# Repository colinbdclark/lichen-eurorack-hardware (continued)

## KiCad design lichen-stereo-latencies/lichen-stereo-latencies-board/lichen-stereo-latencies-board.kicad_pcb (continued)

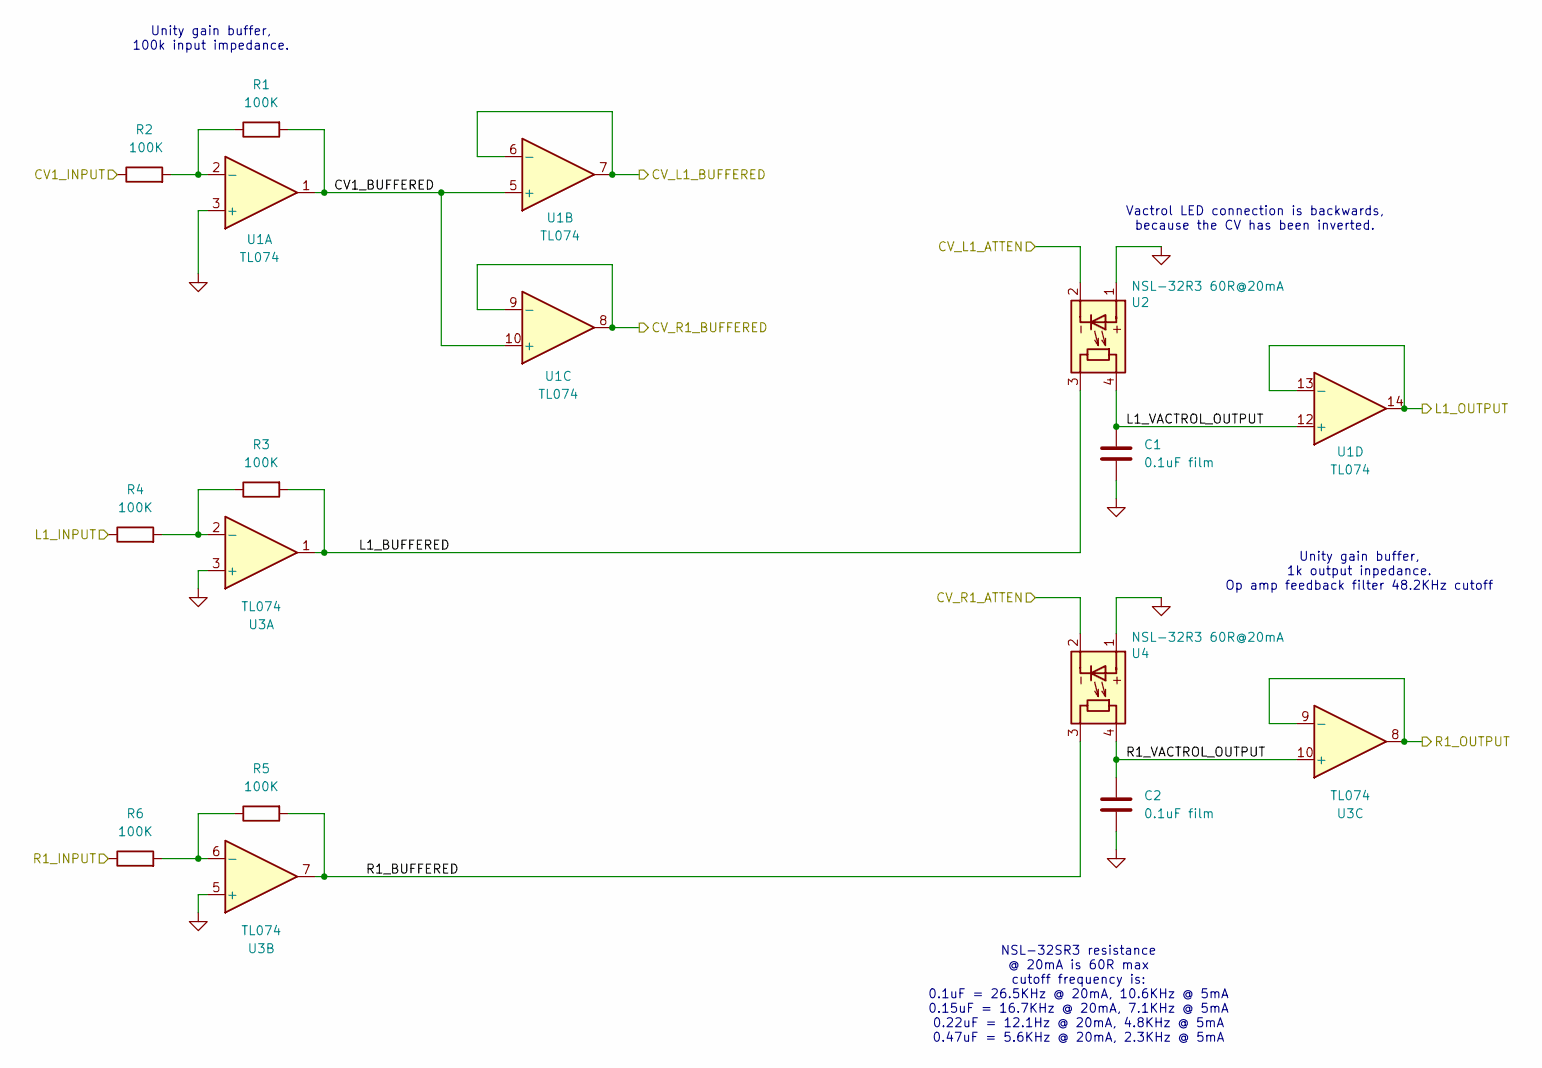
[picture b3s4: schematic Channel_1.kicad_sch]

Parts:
C1, C2: 0.1uF film; C_Rect_L7.2mm_W2.5mm_P5.00mm_FKS2_FKP2_MKS2_MKP2
R1, R2, R3, R4, R5, R6: 100K; R_0402_1005Metric; Part Number 0402WGF1003TCE; LCSC C25741
U1, U3: TL074; SOIC-14_3.9x8.7mm_P1.27mm; Part Number TL074IDR; LCSC C6964
U2, U4: NSL-32R3 60R@20mA; NSL-32; Part Number NSL-32SR3

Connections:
/Channel 1/CV1_BUFFERED: R1.2, U1.1, U1.5 (+), U1.10 (+)
/Channel 1/L1_BUFFERED: R3.2, U2.3 (R), U3.1
/Channel 1/L1_OUTPUT: U1.13 (-), U1.14; also elsewhere on the board
/Channel 1/L1_VACTROL_OUTPUT: C1.1, U1.12 (+), U2.4 (R)
/Channel 1/R1_BUFFERED: R5.2, U3.7, U4.3 (R)
/Channel 1/R1_VACTROL_OUTPUT: C2.1, U3.10 (+), U4.4 (R)
CV1_INPUT: R2.1; also elsewhere on the board
CV_L1_ATTEN: U2.2 (K); also elsewhere on the board
CV_L1_BUFFERED: U1.6 (-), U1.7; also elsewhere on the board
CV_R1_ATTEN: U4.2 (K); also elsewhere on the board
CV_R1_BUFFERED: U1.8, U1.9 (-); also elsewhere on the board
GND: C1.2, C2.2, U1.3 (+), U2.1 (A), U3.3 (+), U3.5 (+), U4.1 (A); also elsewhere on the board
L1_INPUT: R4.1; also elsewhere on the board
unnamed: R1.1, R2.2, U1.2 (-)
unnamed: R3.1, R4.2, U3.2 (-)
unnamed: R5.1, R6.2, U3.6 (-)
R1_INPUT: R6.1; also elsewhere on the board
R1_OUTPUT: U3.8, U3.9 (-); also elsewhere on the board

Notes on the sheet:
Unity gain buffer, 100k input impedance.
Unity gain buffer, 1k output inpedance. Op amp feedback filter 48.2KHz cutoff
NSL-32SR3 resistance @ 20mA is 60R max cutoff frequency is: 0.1uF = 26.5KHz @ 20mA, 10.6KHz @ 5mA 0.15uF = 16.7KHz @ 20mA, 7.1KHz @ 5mA 0.22uF = 12.1Hz @ 20mA, 4.8KHz @ 5mA 0.47uF = 5.6KHz @ 20mA, 2.3KHz @ 5mA
Vactrol LED connection is backwards, because the CV has been inverted.

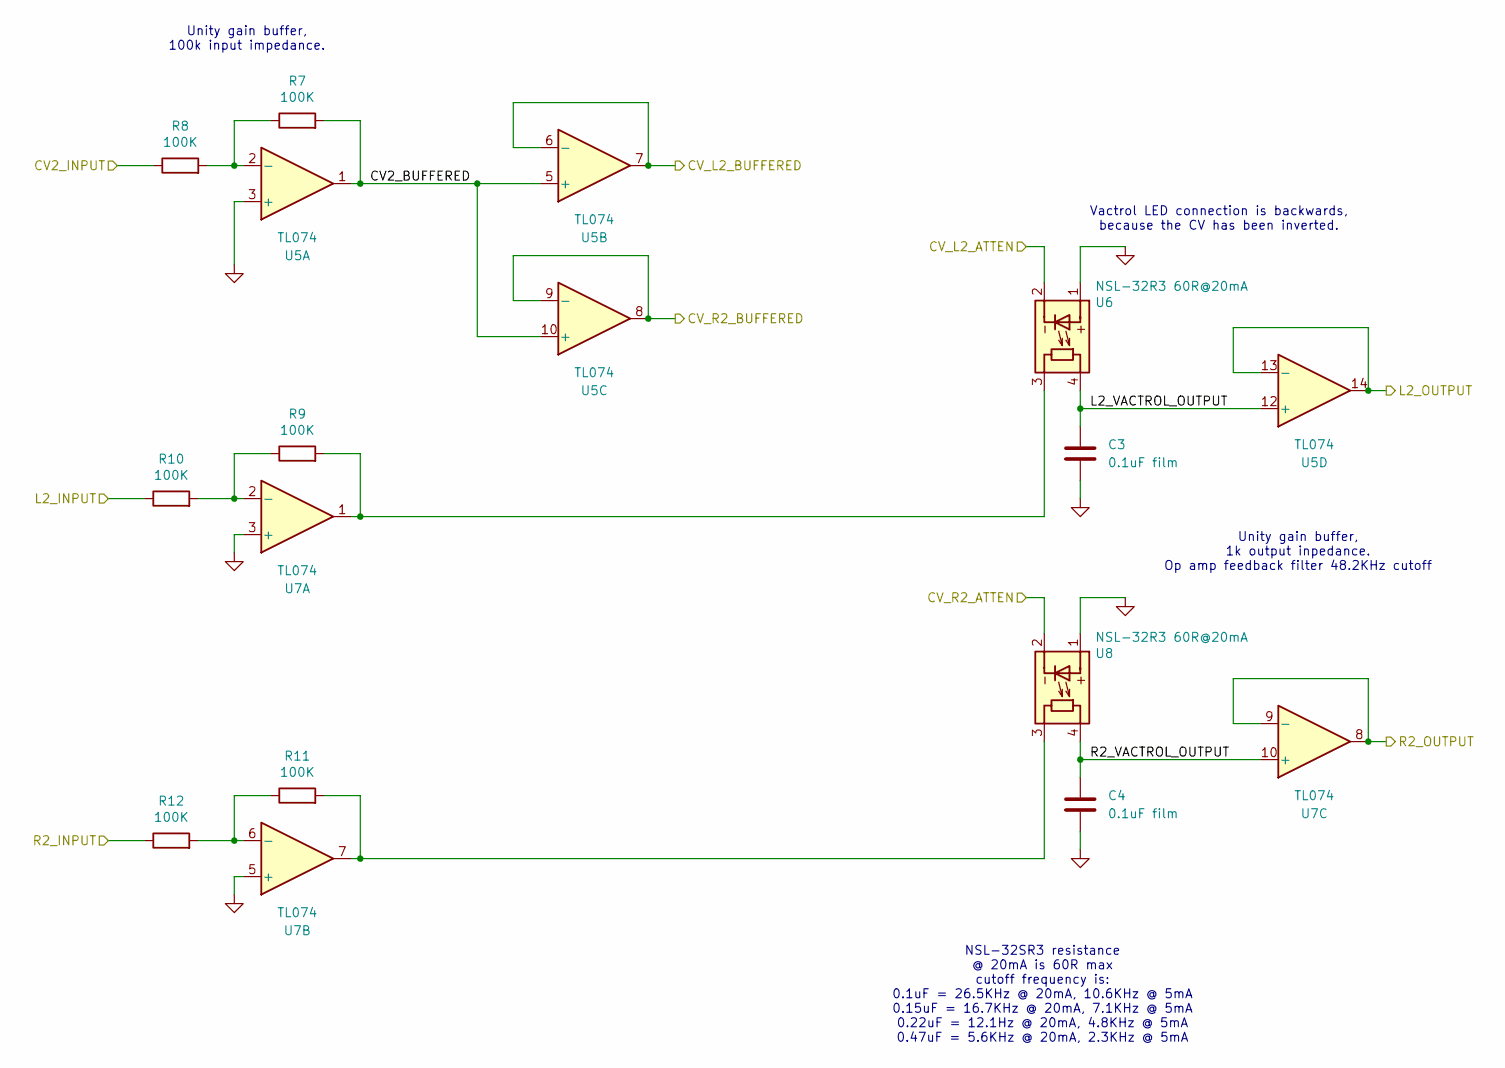
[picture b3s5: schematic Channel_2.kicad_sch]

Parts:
C3, C4: 0.1uF film; C_Rect_L7.2mm_W2.5mm_P5.00mm_FKS2_FKP2_MKS2_MKP2
R7, R8, R9, R10, R11, R12: 100K; R_0402_1005Metric; Part Number 0402WGF1003TCE; LCSC C25741
U5, U7: TL074; SOIC-14_3.9x8.7mm_P1.27mm; Part Number TL074IDR; LCSC C6964
U6, U8: NSL-32R3 60R@20mA; NSL-32; Part Number NSL-32SR3

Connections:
/Channel 2/CV2_BUFFERED: R7.2, U5.1, U5.5 (+), U5.10 (+)
/Channel 2/L2_OUTPUT: U5.13 (-), U5.14; also elsewhere on the board
/Channel 2/L2_VACTROL_OUTPUT: C3.1, U5.12 (+), U6.4 (R)
/Channel 2/R2_OUTPUT: U7.8, U7.9 (-); also elsewhere on the board
/Channel 2/R2_VACTROL_OUTPUT: C4.1, U7.10 (+), U8.4 (R)
CV2_INPUT: R8.1; also elsewhere on the board
CV_L2_ATTEN: U6.2 (K); also elsewhere on the board
CV_L2_BUFFERED: U5.6 (-), U5.7; also elsewhere on the board
CV_R2_ATTEN: U8.2 (K); also elsewhere on the board
CV_R2_BUFFERED: U5.8, U5.9 (-); also elsewhere on the board
GND: C3.2, C4.2, U5.3 (+), U6.1 (A), U7.3 (+), U7.5 (+), U8.1 (A); also elsewhere on the board
L2_INPUT: R10.1; also elsewhere on the board
unnamed: R9.2, U6.3 (R), U7.1
unnamed: R11.2, U7.7, U8.3 (R)
unnamed: R7.1, R8.2, U5.2 (-)
unnamed: R9.1, R10.2, U7.2 (-)
unnamed: R11.1, R12.2, U7.6 (-)
R2_INPUT: R12.1; also elsewhere on the board

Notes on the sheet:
NSL-32SR3 resistance @ 20mA is 60R max cutoff frequency is: 0.1uF = 26.5KHz @ 20mA, 10.6KHz @ 5mA 0.15uF = 16.7KHz @ 20mA, 7.1KHz @ 5mA 0.22uF = 12.1Hz @ 20mA, 4.8KHz @ 5mA 0.47uF = 5.6KHz @ 20mA, 2.3KHz @ 5mA
Unity gain buffer, 1k output inpedance. Op amp feedback filter 48.2KHz cutoff
Unity gain buffer, 100k input impedance.
Vactrol LED connection is backwards, because the CV has been inverted.

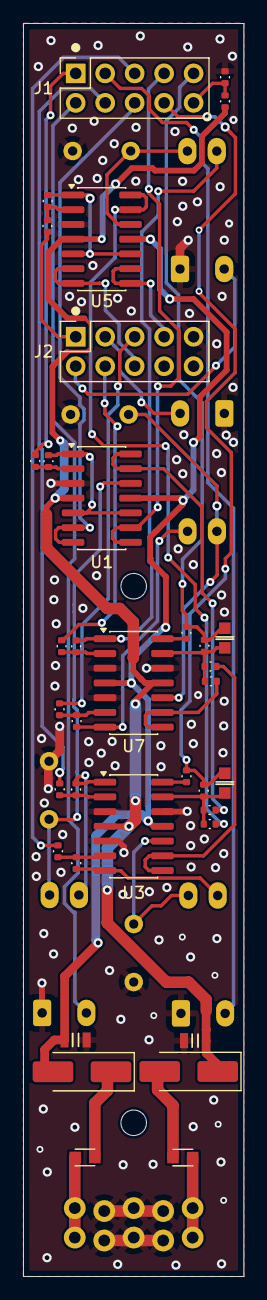
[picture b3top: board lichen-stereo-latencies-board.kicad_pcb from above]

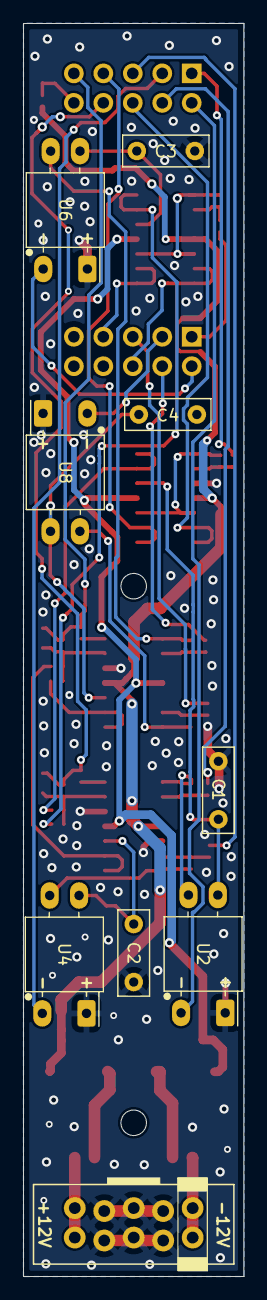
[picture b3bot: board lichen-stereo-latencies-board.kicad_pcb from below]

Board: 2 copper layers, 19.0 x 108.0 mm, 47 parts (9 on the bottom side), 48 nets.

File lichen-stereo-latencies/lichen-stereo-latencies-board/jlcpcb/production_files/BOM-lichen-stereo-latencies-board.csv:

Comment,Designator,Footprint,LCSC,Quantity
1K,"R15,R19",R_0402_1005Metric,C11702,2
FerriteBead_0603_2A,"L1,L2",R_0603,C14709,2
33pF C0G,"C5,C6",C_0603,C1663,2
100K,"R1,R10,R11,R12,R13,R14,R16,R17,R18,R2,R20,R3,R4,R5,R6,R7,R8,R9",R_0402_1005Metric,C25741,18
10K,R21,R_0402_1005Metric,C25744,1
12K,R22,R_0402_1005Metric,C25752,1
10uF,"C7,C8",C_0805,C440198,2
TL074,"U1,U3,U5,U7",SOIC-14_3.9x8.7mm_P1.27mm,C6964,4
Schottky,"D1,D2",D_SMA_Handsoldering,C8678,2

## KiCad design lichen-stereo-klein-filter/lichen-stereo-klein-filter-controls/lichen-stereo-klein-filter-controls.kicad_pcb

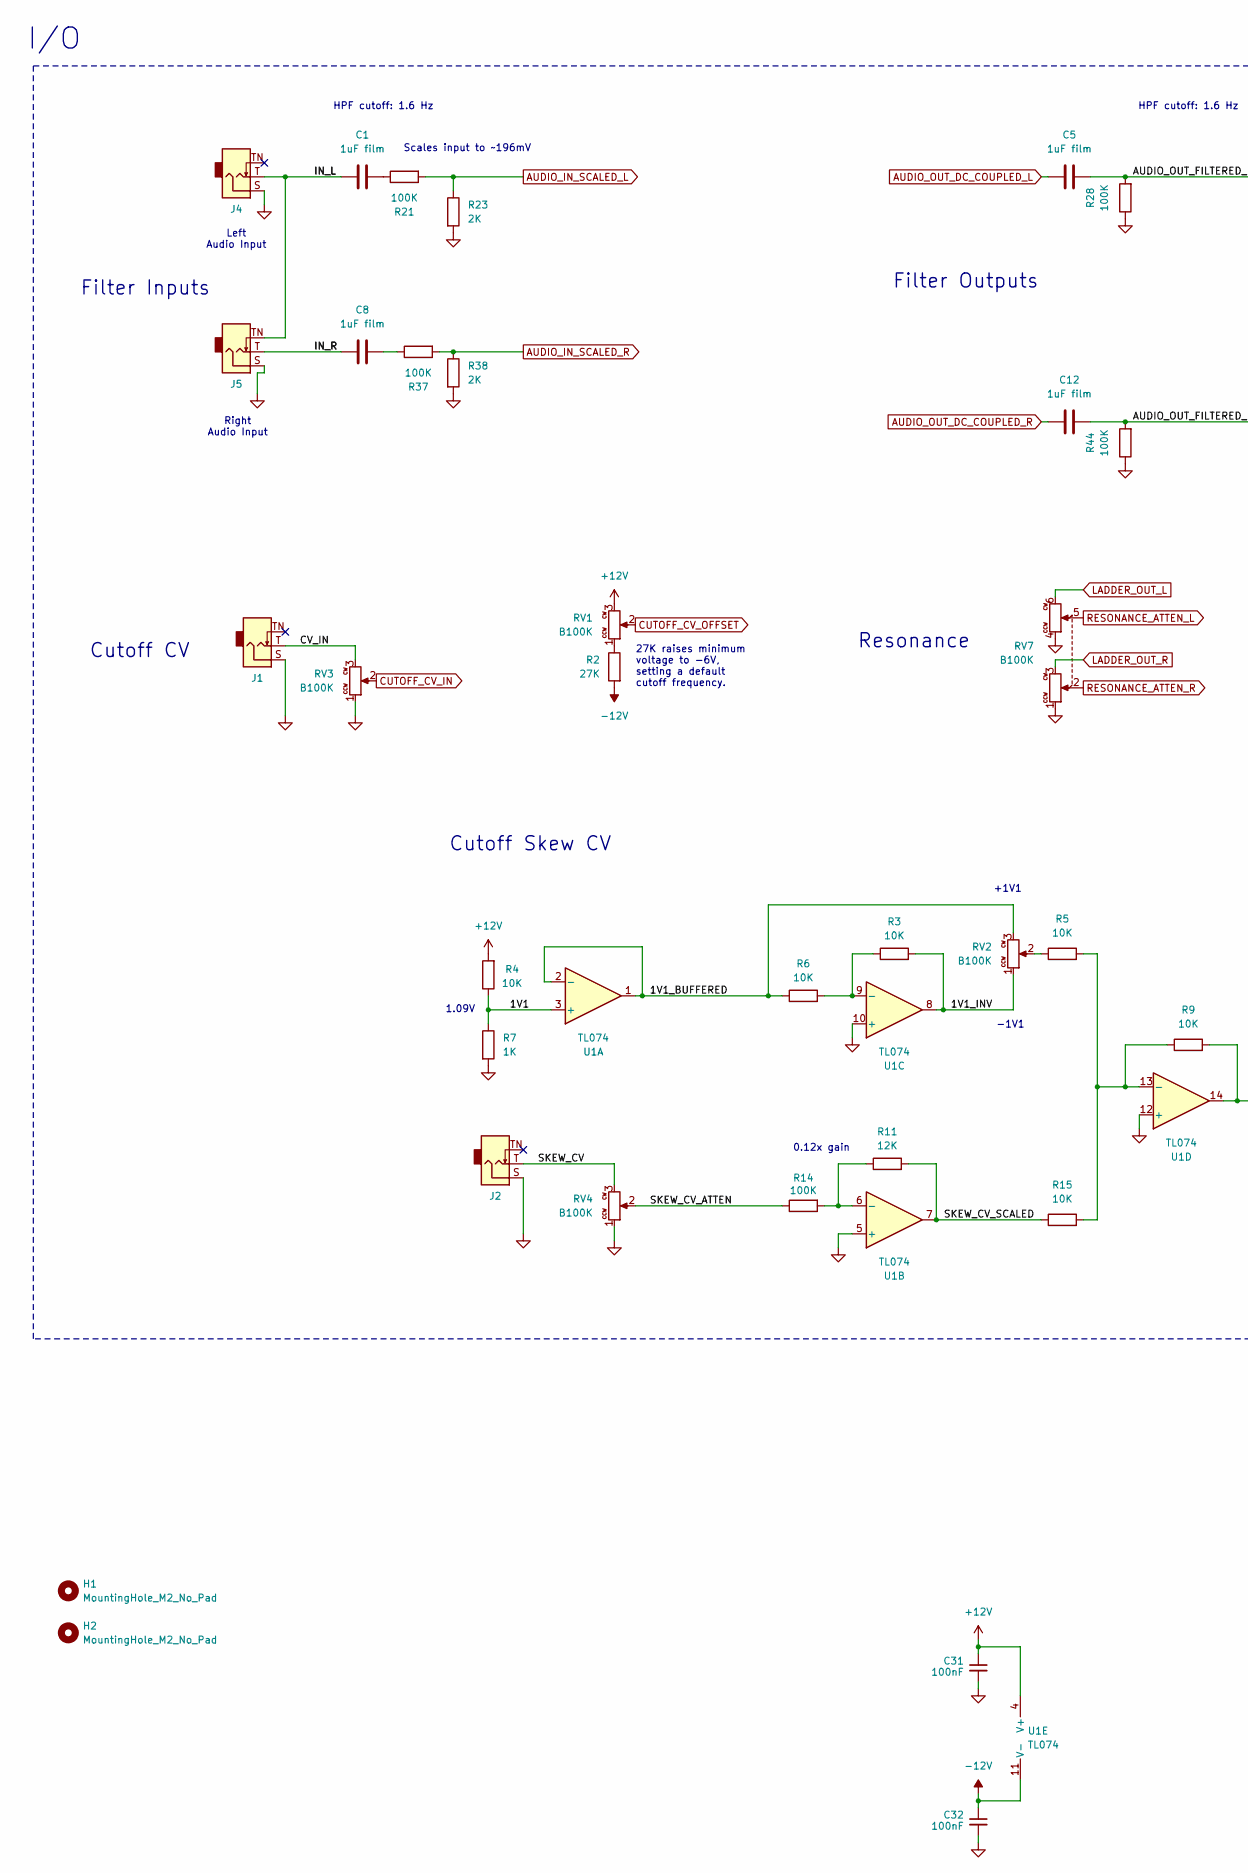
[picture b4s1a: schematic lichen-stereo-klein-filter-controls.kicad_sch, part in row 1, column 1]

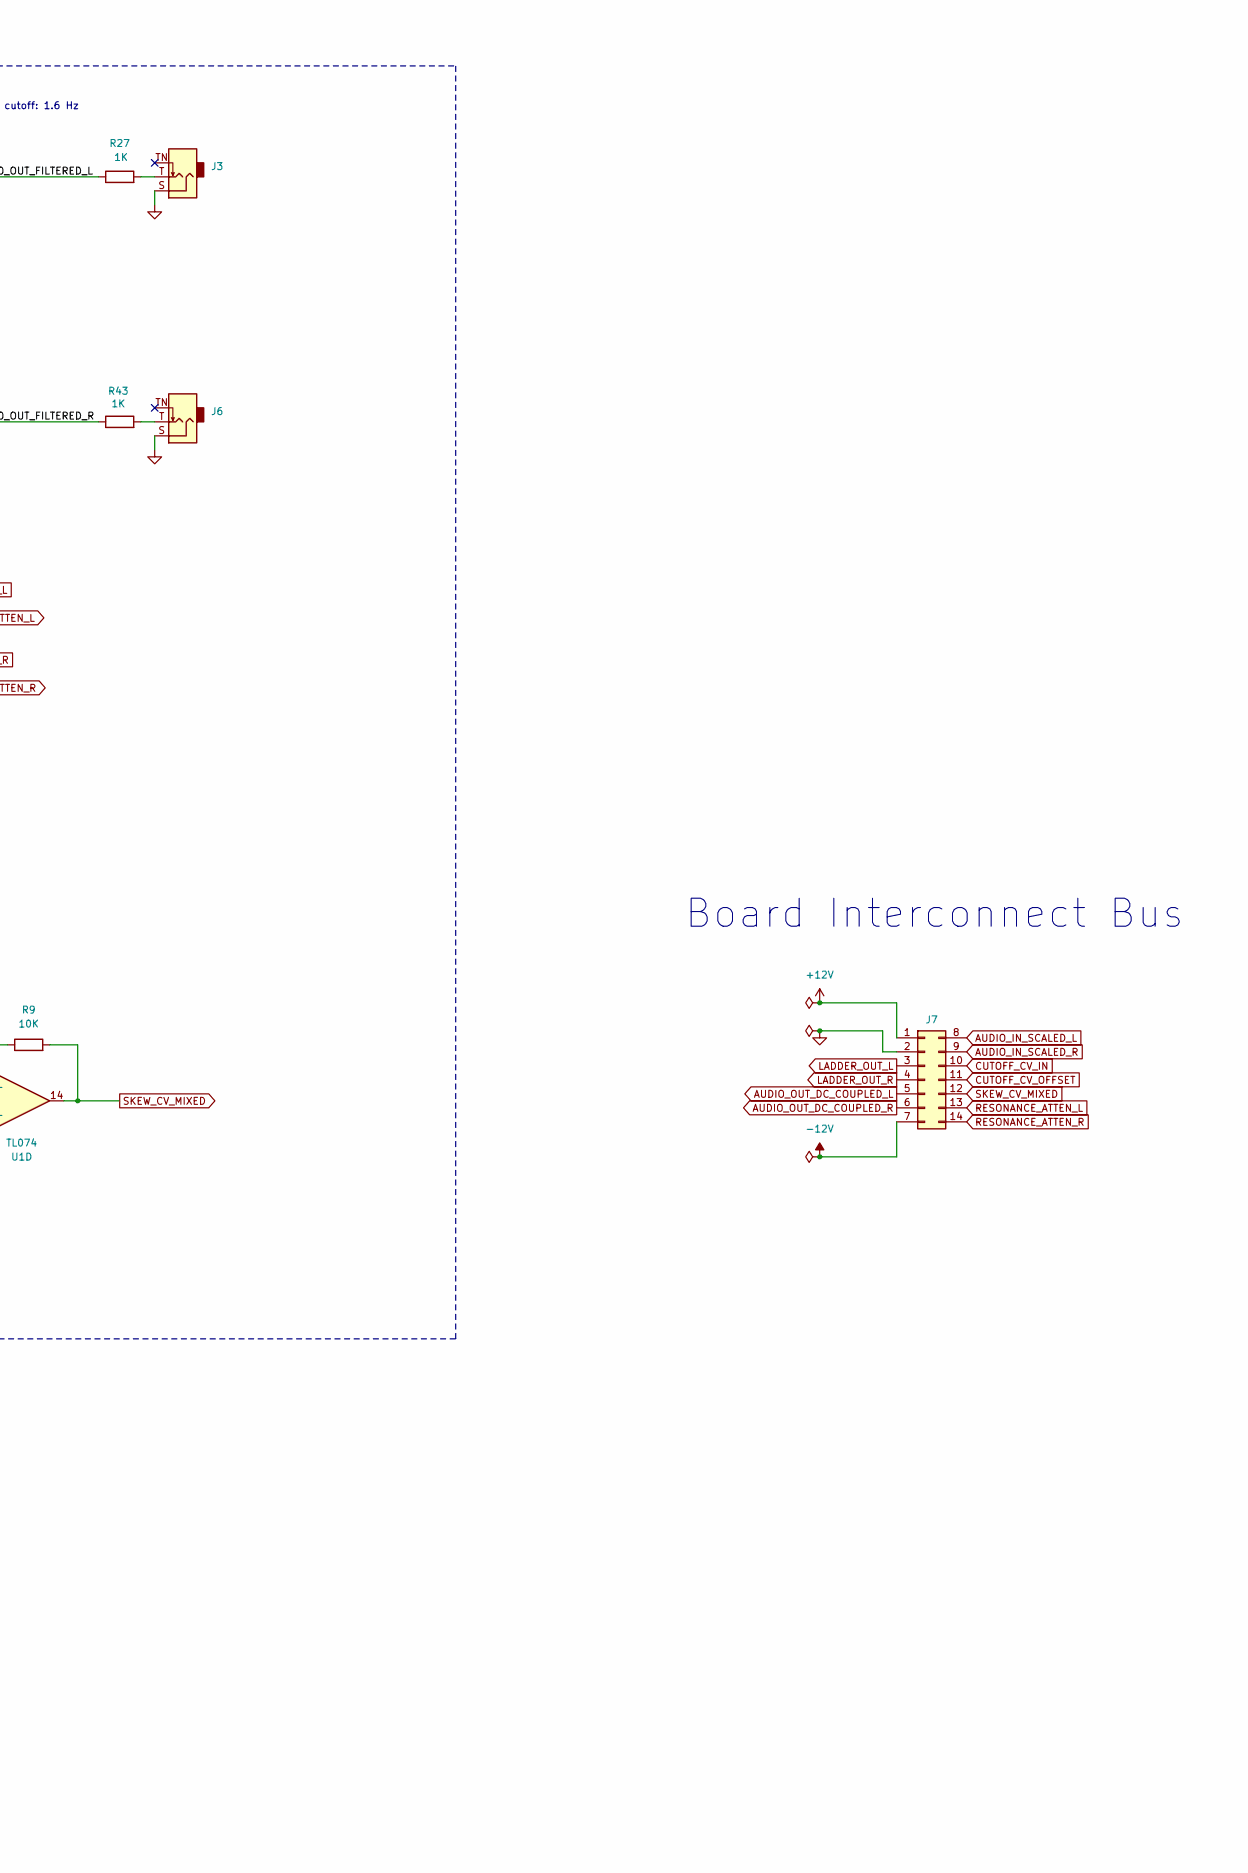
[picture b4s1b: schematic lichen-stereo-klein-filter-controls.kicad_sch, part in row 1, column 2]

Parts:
C1, C5, C8, C12: 1uF film; C_Rect_L7.2mm_W2.5mm_P5.00mm_FKS2_FKP2_MKS2_MKP2
C31, C32: 100nF; C_0402_1005Metric_small_pads; Part Number CL05B104KB54PNC; LCSC C307331
H1, H2: MountingHole_M2_No_Pad; MountingHole_2.2mm_M2
J1, J2: Thonkiconn_Mono_Audio_Jack; Audio_Jack_Thonkiconn_Mono; Part Number WQP518MA/PJ398SM
J3, J6: Thonkiconn_Mono_Audio_Jack; Audio_Jack_Thonkiconn_Mono_Right_Overhang; Part Number WQP518MA/PJ398SM
J4, J5: Thonkiconn_Mono_Audio_Jack; Audio_Jack_Thonkiconn_Mono_Left_Overhang; Part Number WQP518MA/PJ398SM
J7: 02x07 Socket; PinSocket_2x07_P2.54mm_Vertical_SMD; Part Number 2.54-2*7PFemale Headers; LCSC C84005
R2: 27K; R_0603; Part Number 0603WAF2702T5E; LCSC C22967
R3, R6, R9, R15: 10K; R_0603; Part Number 0603WAF1002T5E; LCSC C25804
R4, R5: 10K; R_0603; Part Number 0603WAF1002T5E; JLCPCB ID C25804
R7, R27, R43: 1K; R_0603; Part Number 0603WAF1001T5E; LCSC C21190
R11: 12K; R_0603; Part Number 0603WAF1202T5E; LCSC C22790
R14, R21, R28, R37, R44: 100K; R_0603; Part Number 0603WAF1003T5E; LCSC C25803
R23, R38: 2K; R_0603; Part Number 0603WAF2001T5E; LCSC C22975
RV1, RV2, RV3, RV4: B100K; Potentiometer_Alpha_RD901_Eurorack; Part Number RD901F-40
RV7: B100K; Potentiometer_Alpha_RD902F-40-00D_Dual_Vertical; Part Number RD90F-40
U1: TL074; SOIC-14_3.9x8.7mm_P1.27mm; Part Number TL074IDR; LCSC C6964

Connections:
+12V: C31.1, J7.1, R4.2, RV1.3, U1.4 (V+)
-12V: C32.1, J7.7, R2.2, U1.11 (V-)
/1V1: R4.1, R7.1, U1.3 (+)
/1V1_BUFFERED: R6.1, RV2.3, U1.1, U1.2 (-)
/1V1_INV: R3.2, RV2.1, U1.8
/AUDIO_OUT_FILTERED_L: C5.2, R27.1, R28.2
/AUDIO_OUT_FILTERED_R: C12.2, R43.1, R44.2
/CV_IN: J1.T, RV3.3
/IN_L: C1.1, J4.T, J5.TN
/IN_R: C8.1, J5.T
/SKEW_CV: J2.T, RV4.3
/SKEW_CV_ATTEN: R14.1, RV4.2
/SKEW_CV_SCALED: R11.2, R15.1, U1.7
AUDIO_IN_SCALED_L: J7.8, R21.2, R23.1
AUDIO_IN_SCALED_R: J7.9, R37.2, R38.1
AUDIO_OUT_DC_COUPLED_L: C5.1, J7.5
AUDIO_OUT_DC_COUPLED_R: C12.1, J7.6
CUTOFF_CV_IN: J7.10, RV3.2
CUTOFF_CV_OFFSET: J7.11, RV1.2
GND: C31.2, C32.2, J1.S, J2.S, J3.S, J4.S, J5.S, J6.S, J7.2, R7.2, R23.2, R28.1, R38.2, R44.1, RV3.1, RV4.1, RV7.1, RV7.4, U1.5 (+), U1.10 (+), U1.12 (+)
LADDER_OUT_L: J7.3, RV7.6
LADDER_OUT_R: J7.4, RV7.3
unnamed: C1.2, R21.1
unnamed: C8.2, R37.1
unnamed: J3.T, R27.2
unnamed: J6.T, R43.2
unnamed: R2.1, RV1.1
unnamed: R5.1, RV2.2
unnamed: R11.1, R14.2, U1.6 (-)
unnamed: R3.1, R6.2, U1.9 (-)
unnamed: R5.2, R9.1, R15.2, U1.13 (-)
RESONANCE_ATTEN_L: J7.13, RV7.5
RESONANCE_ATTEN_R: J7.14, RV7.2
SKEW_CV_MIXED: J7.12, R9.2, U1.14

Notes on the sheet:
Filter Outputs
HPF cutoff: 1.6 Hz
Resonance
Cutoff Skew CV
I/O
Scales input to ~196mV
Left Audio Input
Cutoff CV
-1V1
+1V1
Filter Inputs
0.12x gain
Right Audio Input
Board Interconnect Bus
1.09V
27K raises minimum voltage to -6V, setting a default cutoff frequency.

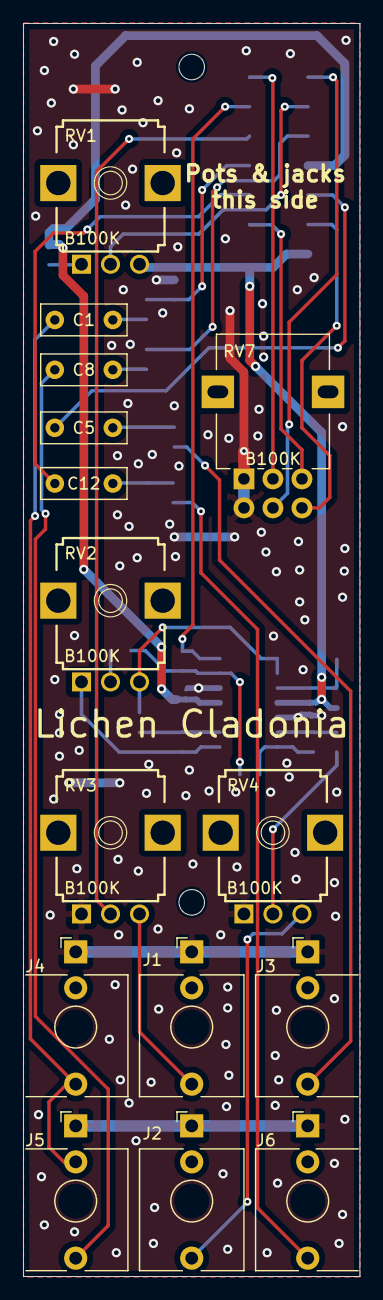
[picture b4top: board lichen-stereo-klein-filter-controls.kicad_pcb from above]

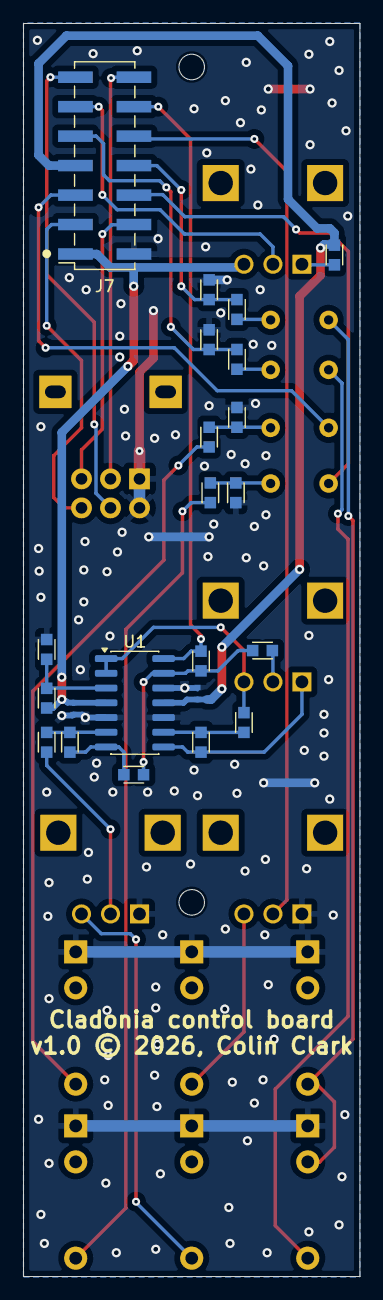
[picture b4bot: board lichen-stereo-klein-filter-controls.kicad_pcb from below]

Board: 2 copper layers, 29.0 x 108.0 mm, 39 parts (22 on the bottom side), 34 nets.

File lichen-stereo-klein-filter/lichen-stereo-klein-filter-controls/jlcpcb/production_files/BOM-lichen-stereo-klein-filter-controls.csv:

Comment,Designator,Footprint,LCSC,Quantity
1K,"R27,R43,R7",R_0603,C21190,3
12K,R11,R_0603,C22790,1
27K,R2,R_0603,C22967,1
2K,"R23,R38",R_0603,C22975,2
100K,"R14,R21,R28,R37,R44",R_0603,C25803,5
10K,"R15,R3,R4,R5,R6,R9",R_0603,C25804,6
100nF,"C31,C32",C_0402_1005Metric_small_pads,C307331,2
TL074,U1,SOIC-14_3.9x8.7mm_P1.27mm,C6964,1
02x07 Socket,J7,PinSocket_2x07_P2.54mm_Vertical_SMD,C84005,1

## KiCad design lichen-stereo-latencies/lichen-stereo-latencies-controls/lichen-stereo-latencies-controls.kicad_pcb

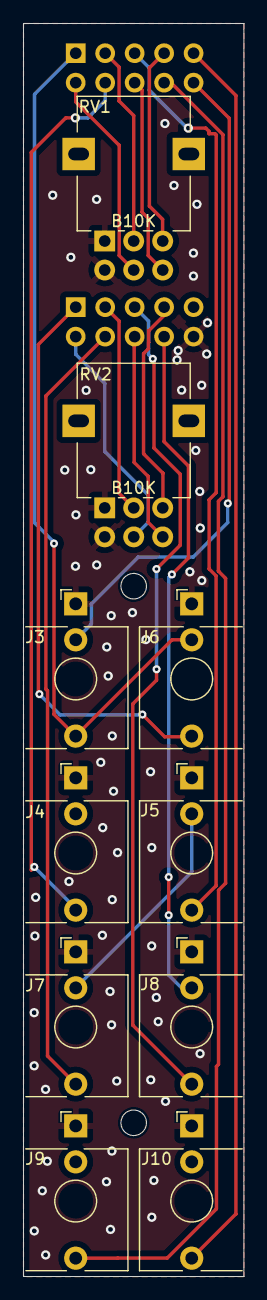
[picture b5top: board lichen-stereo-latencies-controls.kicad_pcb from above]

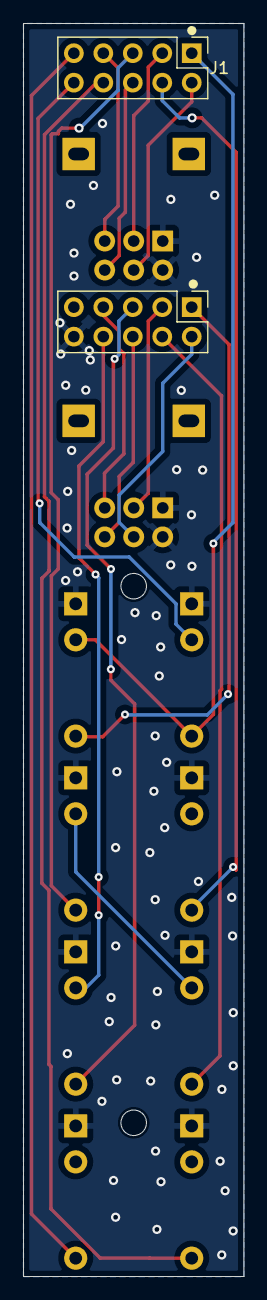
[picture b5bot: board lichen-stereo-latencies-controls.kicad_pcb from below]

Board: 2 copper layers, 19.0 x 108.0 mm, 14 parts (2 on the bottom side), 20 nets.

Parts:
H1, H2: MountingHole_M2_No_Pad; MountingHole_2.2mm_M2
J1: 02x05 Pins; PinHeader_2x05_P2.54mm_Vertical
J2: 2x5 Pins; PinHeader_2x05_P2.54mm_Vertical
J3, J4, J7, J9: Thonkiconn_Mono_Audio_Jack; Audio_Jack_Thonkiconn_Mono_Left_Overhang
J5, J6, J8, J10: Thonkiconn_Mono_Audio_Jack; Audio_Jack_Thonkiconn_Mono_Right_Overhang
RV1, RV2: B10K; Potentiometer_Alpha_RD902F-40-00D_Dual_Vertical

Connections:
CV1_INPUT: J1.1, J3.T, J6.TN
CV2_INPUT: J2.1, J6.T
CV_L1_ATTEN: J1.2, RV1.5
CV_L1_BUFFERED: J1.6, RV1.6
CV_L2_ATTEN: J2.2, RV2.5
CV_L2_BUFFERED: J2.6, RV2.6
CV_NORM_5V: J1.10, J3.TN
CV_R1_ATTEN: J1.3, RV1.2
CV_R1_BUFFERED: J1.7, RV1.3
CV_R2_ATTEN: J2.3, RV2.2
CV_R2_BUFFERED: J2.7, RV2.3
GND: J2.10, J3.S, J4.S, J5.S, J6.S, J7.S, J8.S, J9.S, J10.S, RV1.1, RV1.4, RV2.1, RV2.4
L1_INPUT: J1.4, J4.T
L1_OUTPUT: J5.TN, J7.TN
L2_INPUT: J2.4, J7.T
L_OUTPUT: J1.8, J9.T
R1_INPUT: J1.5, J5.T
R1_OUTPUT: J2.8, J8.TN
R2_INPUT: J2.5, J8.T
R_OUTPUT: J1.9, J10.T

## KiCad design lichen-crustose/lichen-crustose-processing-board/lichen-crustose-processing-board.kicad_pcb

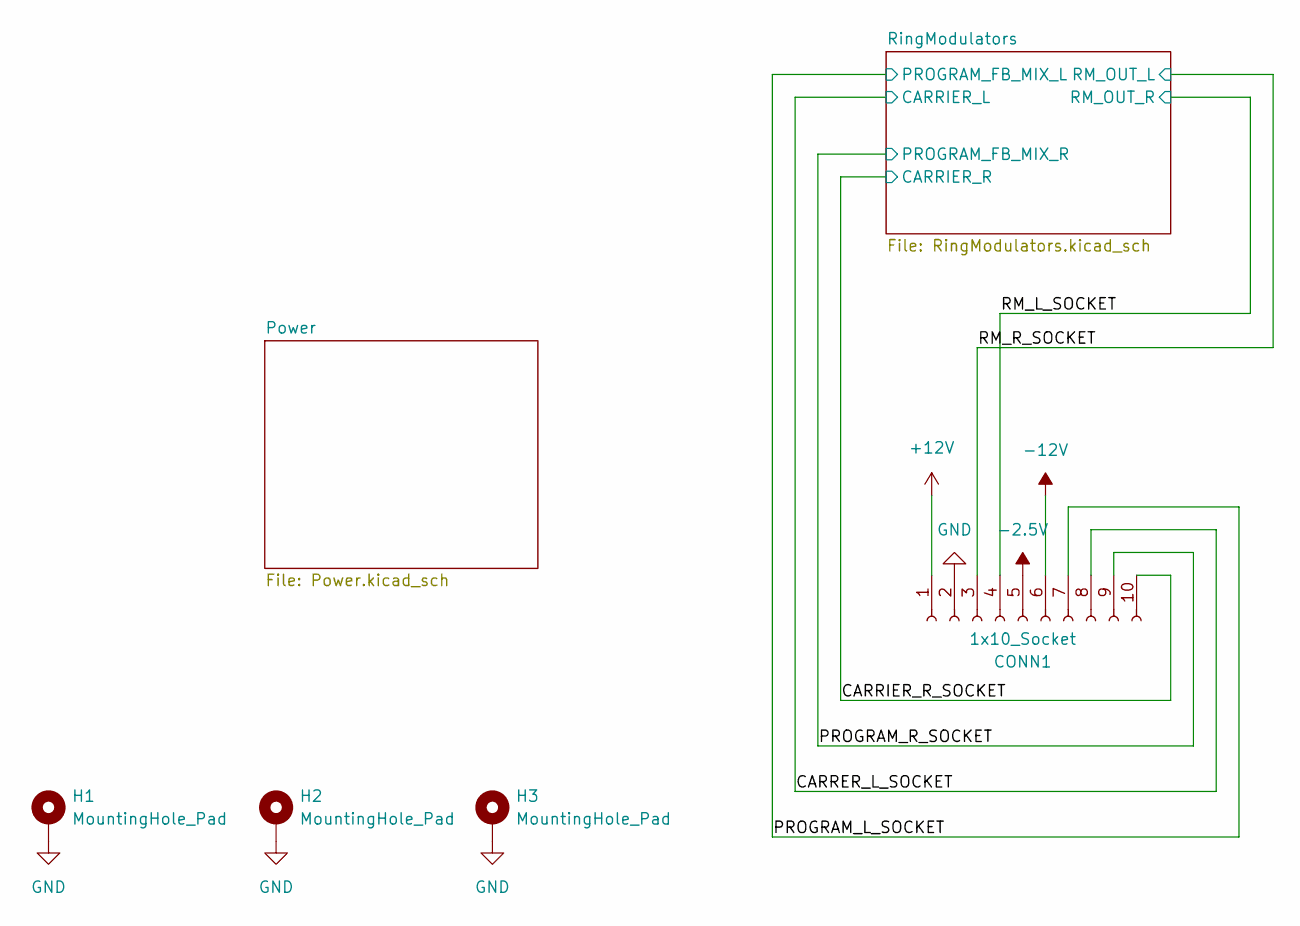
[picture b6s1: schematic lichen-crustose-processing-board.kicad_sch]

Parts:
CONN1: 1x10_Socket; PinSocket_1x10_P2.54mm_Vertical
H1, H2, H3: MountingHole_Pad; MountingHole_2.2mm_M2_Pad

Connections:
+12V: CONN1.1; also elsewhere on the board
-2.5V: CONN1.5; also elsewhere on the board
-12V: CONN1.6; also elsewhere on the board
/CARRER_L_SOCKET: CONN1.8; also elsewhere on the board
/CARRIER_R_SOCKET: CONN1.10; also elsewhere on the board
/PROGRAM_L_SOCKET: CONN1.7; also elsewhere on the board
/PROGRAM_R_SOCKET: CONN1.9; also elsewhere on the board
/RM_L_SOCKET: CONN1.4; also elsewhere on the board
/RM_R_SOCKET: CONN1.3; also elsewhere on the board
GND: CONN1.2, H1.1, H2.1, H3.1; also elsewhere on the board

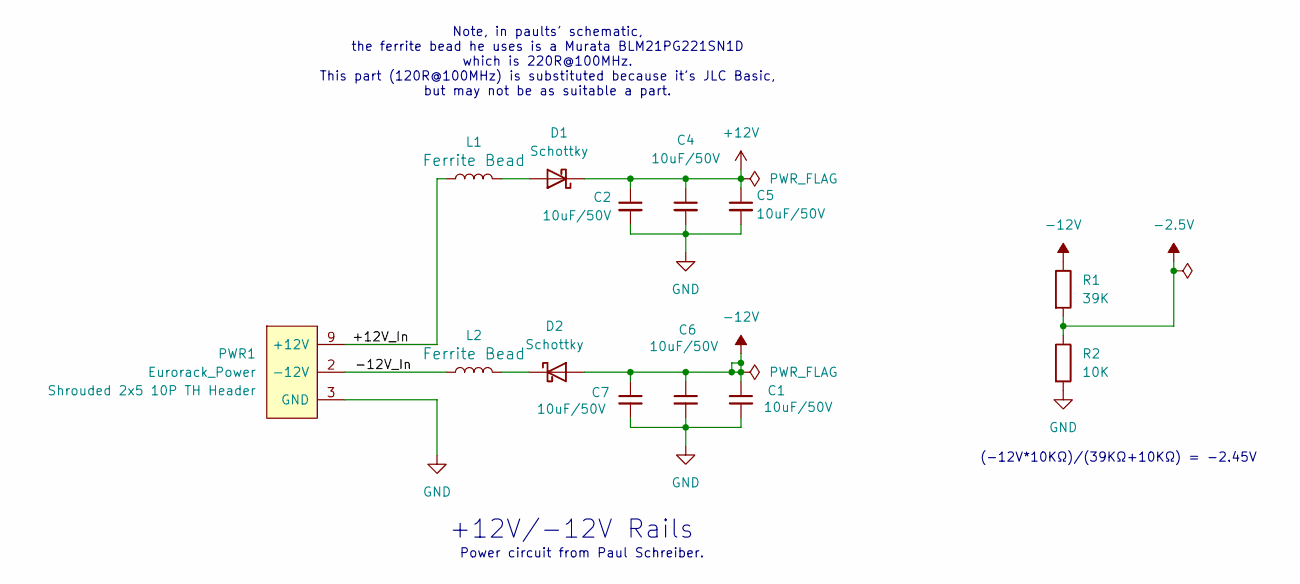
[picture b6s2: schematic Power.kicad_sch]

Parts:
C1, C2, C4, C5, C6, C7: 10uF; C_0805; Part Number GRM21BR61H106KE43L; LCSC C440198
D1, D2: Schottky; D_SMA_Handsoldering; Part Number SS34; LCSC C8678
L1, L2: FerriteBead_0603_2A; R_0603; Part Number BLM18PG121SN1D; LCSC C14709
PWR1: Eurorack_Power; Eurorack_Power_Shrouded_TH_Staggered
R1: 39K; R_0603; Part Number 0603WAF3902T5E; LCSC C23153
R2: 10K; R_0603; Part Number 0603WAF1002T5E; LCSC C25804

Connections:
+12V: C2.1, C4.1, C5.1, D1.1 (K); also elsewhere on the board
-2.5V: R1.2, R2.1; also elsewhere on the board
-12V: C1.1, C6.1, C7.1, D2.2 (A), R1.1; also elsewhere on the board
/Power/+12V_In: L1.1, PWR1.9 (+12V), PWR1.10 (+12V)
/Power/-12V_In: L2.1, PWR1.1 (-12V), PWR1.2 (-12V)
GND: C1.2, C2.2, C4.2, C5.2, C6.2, C7.2, PWR1.3 (GND), PWR1.4 (GND), PWR1.5 (GND), PWR1.6 (GND), PWR1.7 (GND), PWR1.8 (GND), R2.2; also elsewhere on the board
unnamed: D1.2 (A), L1.2
unnamed: D2.1 (K), L2.2

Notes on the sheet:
Note, in paults' schematic, the ferrite bead he uses is a Murata BLM21PG221SN1D which is 220R@100MHz. This part (120R@100MHz) is substituted because it's JLC Basic, but may not be as suitable a part.
(-12V*10KΩ)/(39KΩ+10KΩ) = -2.45V
Power circuit from Paul Schreiber.
+12V/-12V Rails

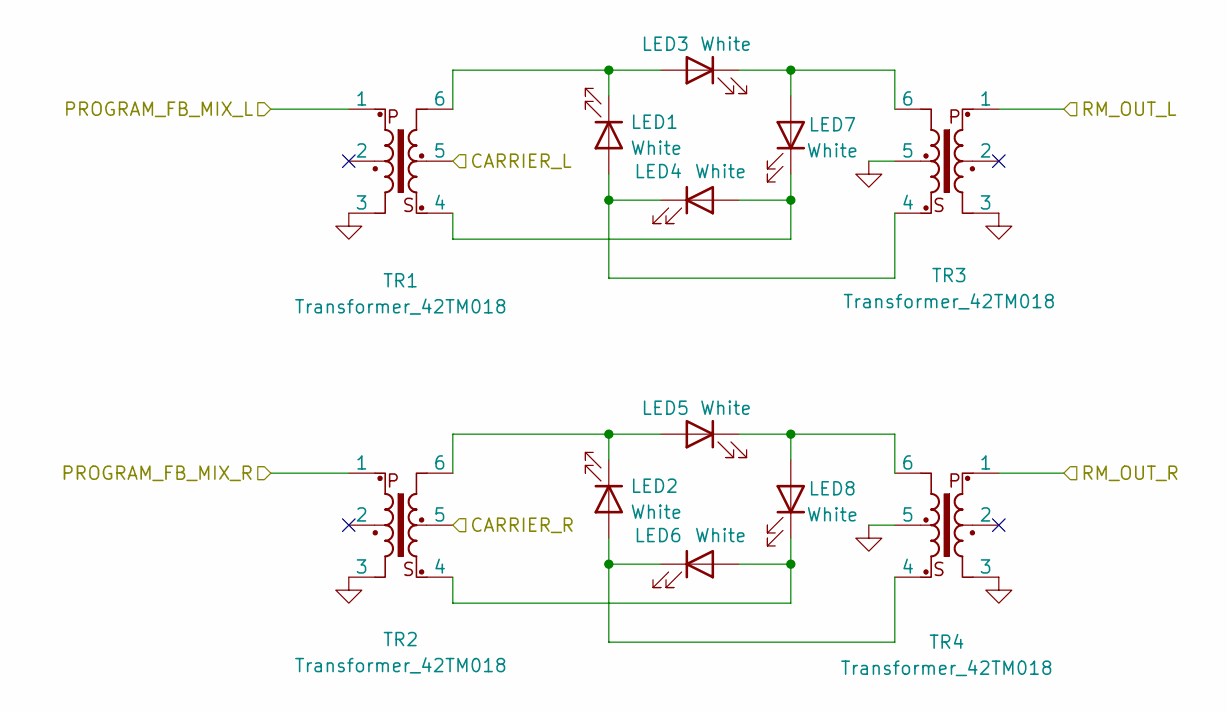
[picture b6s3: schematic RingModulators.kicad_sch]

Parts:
LED1, LED2, LED3, LED4, LED5, LED6, LED7, LED8: White; LED_D3.0mm_Polarity_Indicated
TR1, TR2, TR3, TR4: Transformer_42TM018; 42TM018

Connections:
/CARRER_L_SOCKET: TR1.5; also elsewhere on the board
/CARRIER_R_SOCKET: TR2.5; also elsewhere on the board
/PROGRAM_L_SOCKET: TR1.1; also elsewhere on the board
/PROGRAM_R_SOCKET: TR2.1; also elsewhere on the board
/RM_L_SOCKET: TR4.1; also elsewhere on the board
/RM_R_SOCKET: TR3.1; also elsewhere on the board
GND: TR1.3, TR2.3, TR3.3, TR3.5, TR4.3, TR4.5; also elsewhere on the board
unnamed: LED1.2 (A), LED4.1 (K), TR3.4
unnamed: LED1.1 (K), LED3.2 (A), TR1.6
unnamed: LED2.2 (A), LED6.1 (K), TR4.4
unnamed: LED2.1 (K), LED5.2 (A), TR2.6
unnamed: LED3.1 (K), LED7.2 (A), TR3.6
unnamed: LED4.2 (A), LED7.1 (K), TR1.4
unnamed: LED5.1 (K), LED8.2 (A), TR4.6
unnamed: LED6.2 (A), LED8.1 (K), TR2.4

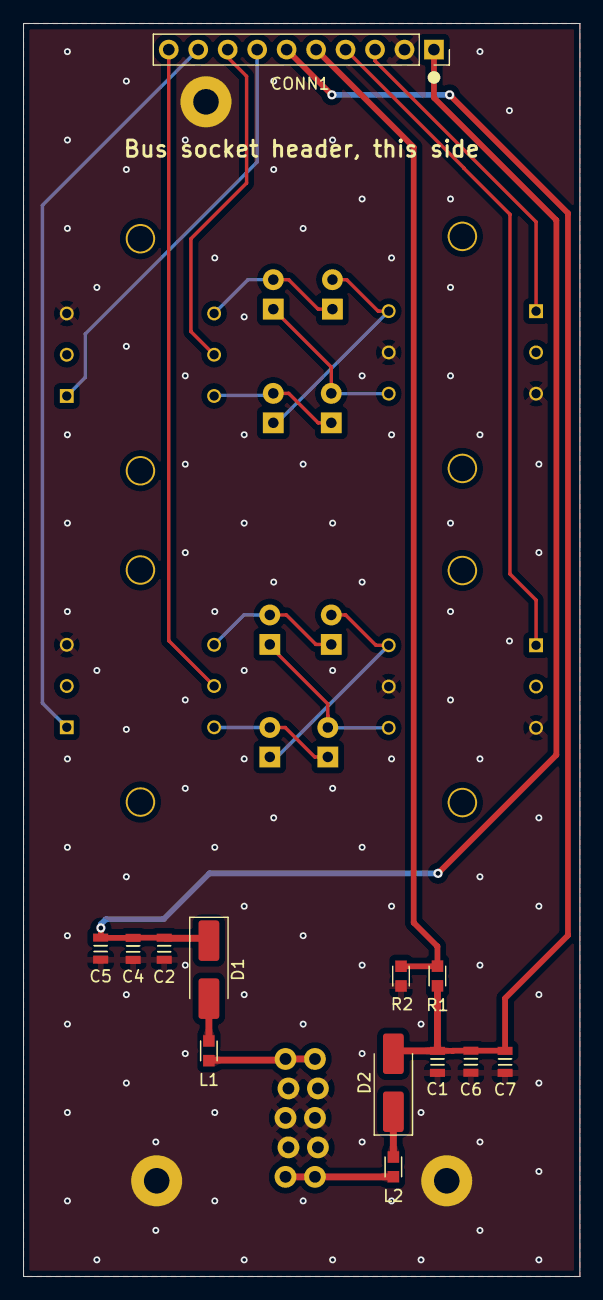
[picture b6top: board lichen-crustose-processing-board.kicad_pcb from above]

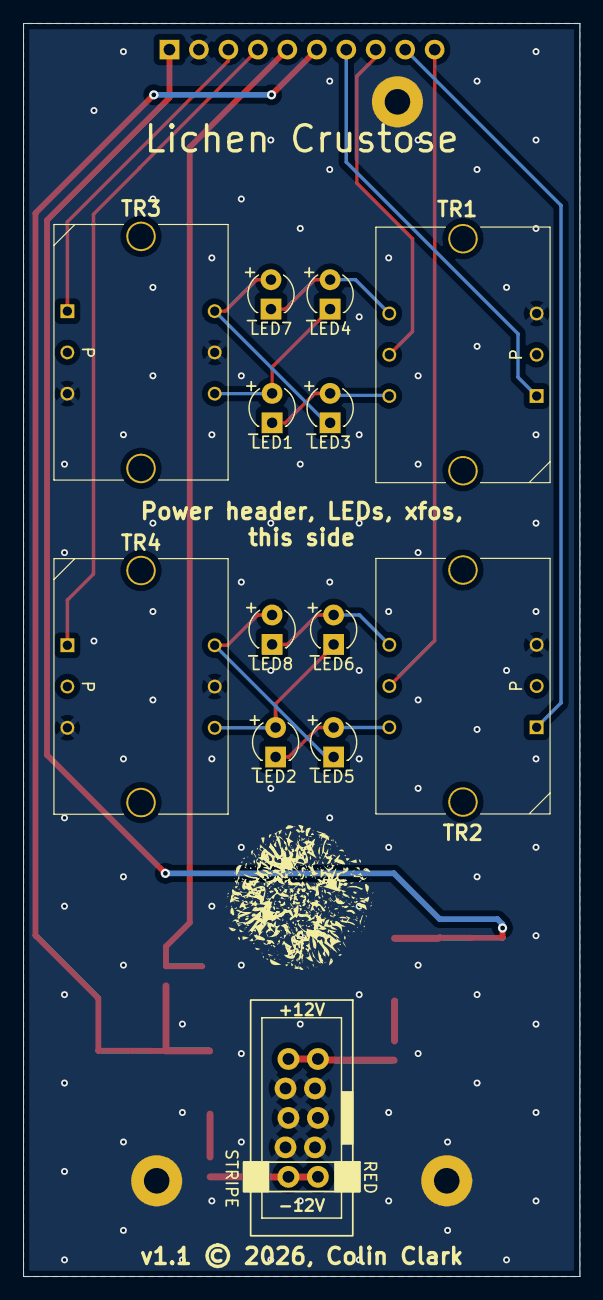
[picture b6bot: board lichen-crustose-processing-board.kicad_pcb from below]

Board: 2 copper layers, 48.0 x 108.0 mm, 29 parts (13 on the bottom side), 22 nets.
